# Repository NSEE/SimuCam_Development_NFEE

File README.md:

##SimuCam Development - N-FEE (LESIA/IAA)

# Repository Description - SimuCam/N-FEE
This repository manages the release of the software packages related with the SimuCam project, focusing on its N-FEE version, whose directly user  is the [LESIA (Laboratoire d’études spatiales et d’instrumentation en astrophysique)](https://lesia.obspm.fr/). This projet is a part of PLATO mission, and it is being developed by the NSEE (Núcleo de Sistemas Eletrônicos Embarcados) team, a laboratory that is part of [IMT (Instituto Mauá de Tecnologia)](https://maua.br/) at São Caetano do Sul, São Paulo, Brazil, in a partnership with [USP-IAG (Instituto de Astronomia, Geofísica e Ciências Atmosféricas)](https://www.iag.usp.br/) , funded by [FAPESP (Fundação de Amparo à Pesquisa do Estado de São Paulo )](https://fapesp.br/).

## Repository Contributors

- [Professor Vanderlei Cunha Parro - Laboratory and Project Coordinator](https://github.com/vparro) (2010-Today)
- [Professor Tiago Sanches da Silva - Software Architect, SW Team Leader and Developer](https://github.com/Tiagoeem) (2017-2020)
- [Engineer Rodrigo De Marca França - VHDL Architect and Developer](https://github.com/rodmarfran) (2017-Today)
- [Engineer Érico Lucas Marques - Project Manager and System Engineer](https://github.com/ericolucasm) (2018-Today)
- [Engineer Alexsander Deucher - SW Developer](https://github.com/adbtx) (2019-2020)
- [Engineer Ricardo Napoli - Test Engineer](https://github.com/rnapoli) (2019-2021)
- [Engineer Cassio Berni - SW Engineer](https://github.com/ccberni) (2019-2020)
- [Engineer Rafael Corsi Ferrão - Hardware Engineer](https://github.com/rafaelcorsi) (2011-2016) 
- [Engineer Thiago Pereira Ricciardi - SW Developer](https://github.com/thiagoricciardi) (2018-Today)

# SimuCam
The SimuCam is an electronic system with 8 independent SpaceWires links, emulating the behavior of PLATO’s cameras (N-FEE and F-FEE), and controlled by Ethernet.
SimuCam will be used by ﬁve diﬀerent teams in the PLATO consortium, each one in a diﬀerent situation, ranging from software development to system integration. 
From the user point of view, SimuCam is able to emulate 6 normal cameras and 4 fast cameras and a spacewire data generator.

SimuCam has 3 different versions, depending on its final use:

|#|Version ID|Final User Lab| Countries|
|:--:|:--:|--|--|
|1|SimuCam/N-FEE | [Lesia (Laboratoire d’études spatiales et d’instrumentation en astrophysique)](https://lesia.obspm.fr/), [IAA (Instituto Astrofísica Andalucía)](https://www.iaa.csic.es/en)| France, Spain
|2|SimuCam/F-FEE | [DLR (Deutsches Zentrum für Luft- und Raumfahrt)](https://www.dlr.de/DE/Home/home_node.html) | Germany
|3|SimuCam/Data Transmission | [IWF (Österreichische Akademie der Wissenschaften)(https://www.iwf.oeaw.ac.at/home/)], [INAF (Istituto Nazionale di Astrofisica)](http://www.inaf.it/it)|Austria, Italy

# PLATO (PLAnetary Transits and Oscillations of stars)
PLATO (PLAnetary Transits and Oscillations of stars) is the third medium-class mission in ESA's Cosmic Vision programme. Its objective is to find and study a large number of extrasolar planetary systems, with emphasis on the properties of terrestrial planets in the habitable zone around solar-like stars. PLATO has also been designed to investigate seismic activity in stars, enabling the precise characterisation of the planet host star, including its age.

More informmation about PLATO mission could be found in the Mission official [website](https://sci.esa.int/web/plato/).

# IMT (Instituto Mauá de Tecnologia)
IMT (Instituto Mauá de Tecnologia) is a private, non-proﬁt organization. Its main objective is to promote technical-scientiﬁc education, technological research and development aiming to provide highly qualiﬁed human resources to contribute to the socioeconomic development of Brazil. IMT was founded on December 11, 1961 its headquarters is located at Rua Pedro de Toledo, 1071 in São Paulo city. The institute maintains two units: the Centro Universitário and the Technical Services and Tests Center and two campi: one in São Paulo city and the other in São Caetano do Sul. The headquarter of the two units is located at IMT campus in São Caetano do Sul at Praça Maua, 1 with a constricted area of 130,000 m2, 12km from São Paulo city center. In this campus the Centro Universitário offers undergraduate courses in Engineering, Design, Administrations and Higher Education Certiﬁcate.

More informmation about IMT could be found in the Institute official [website](https://maua.br/).

# NSEE (Nucleo de Sistemas Eletrônicos Embarcados)
[NSEE (Nucleo de Sistemas Eletrônicos Embarcados)](https://maua.br/pesquisa/grupos-pesquisa/nucleo-sistemas-eletronicos-embarcados/), created on the initiative of the Mauá de Tecnologia Institute (IMT) based on participation in the initial version of INCT INEspaço, has developed research in the area of critical systems with direct application in the aerospace area. Its performance is related to the study of electronic systems that allow solving problems by meeting severe restrictions on communication speed, mass, consumption and real-time processing. Another area of expertise involves the development of multivariable control and signal processing systems, their algorithms and embedded implementations.

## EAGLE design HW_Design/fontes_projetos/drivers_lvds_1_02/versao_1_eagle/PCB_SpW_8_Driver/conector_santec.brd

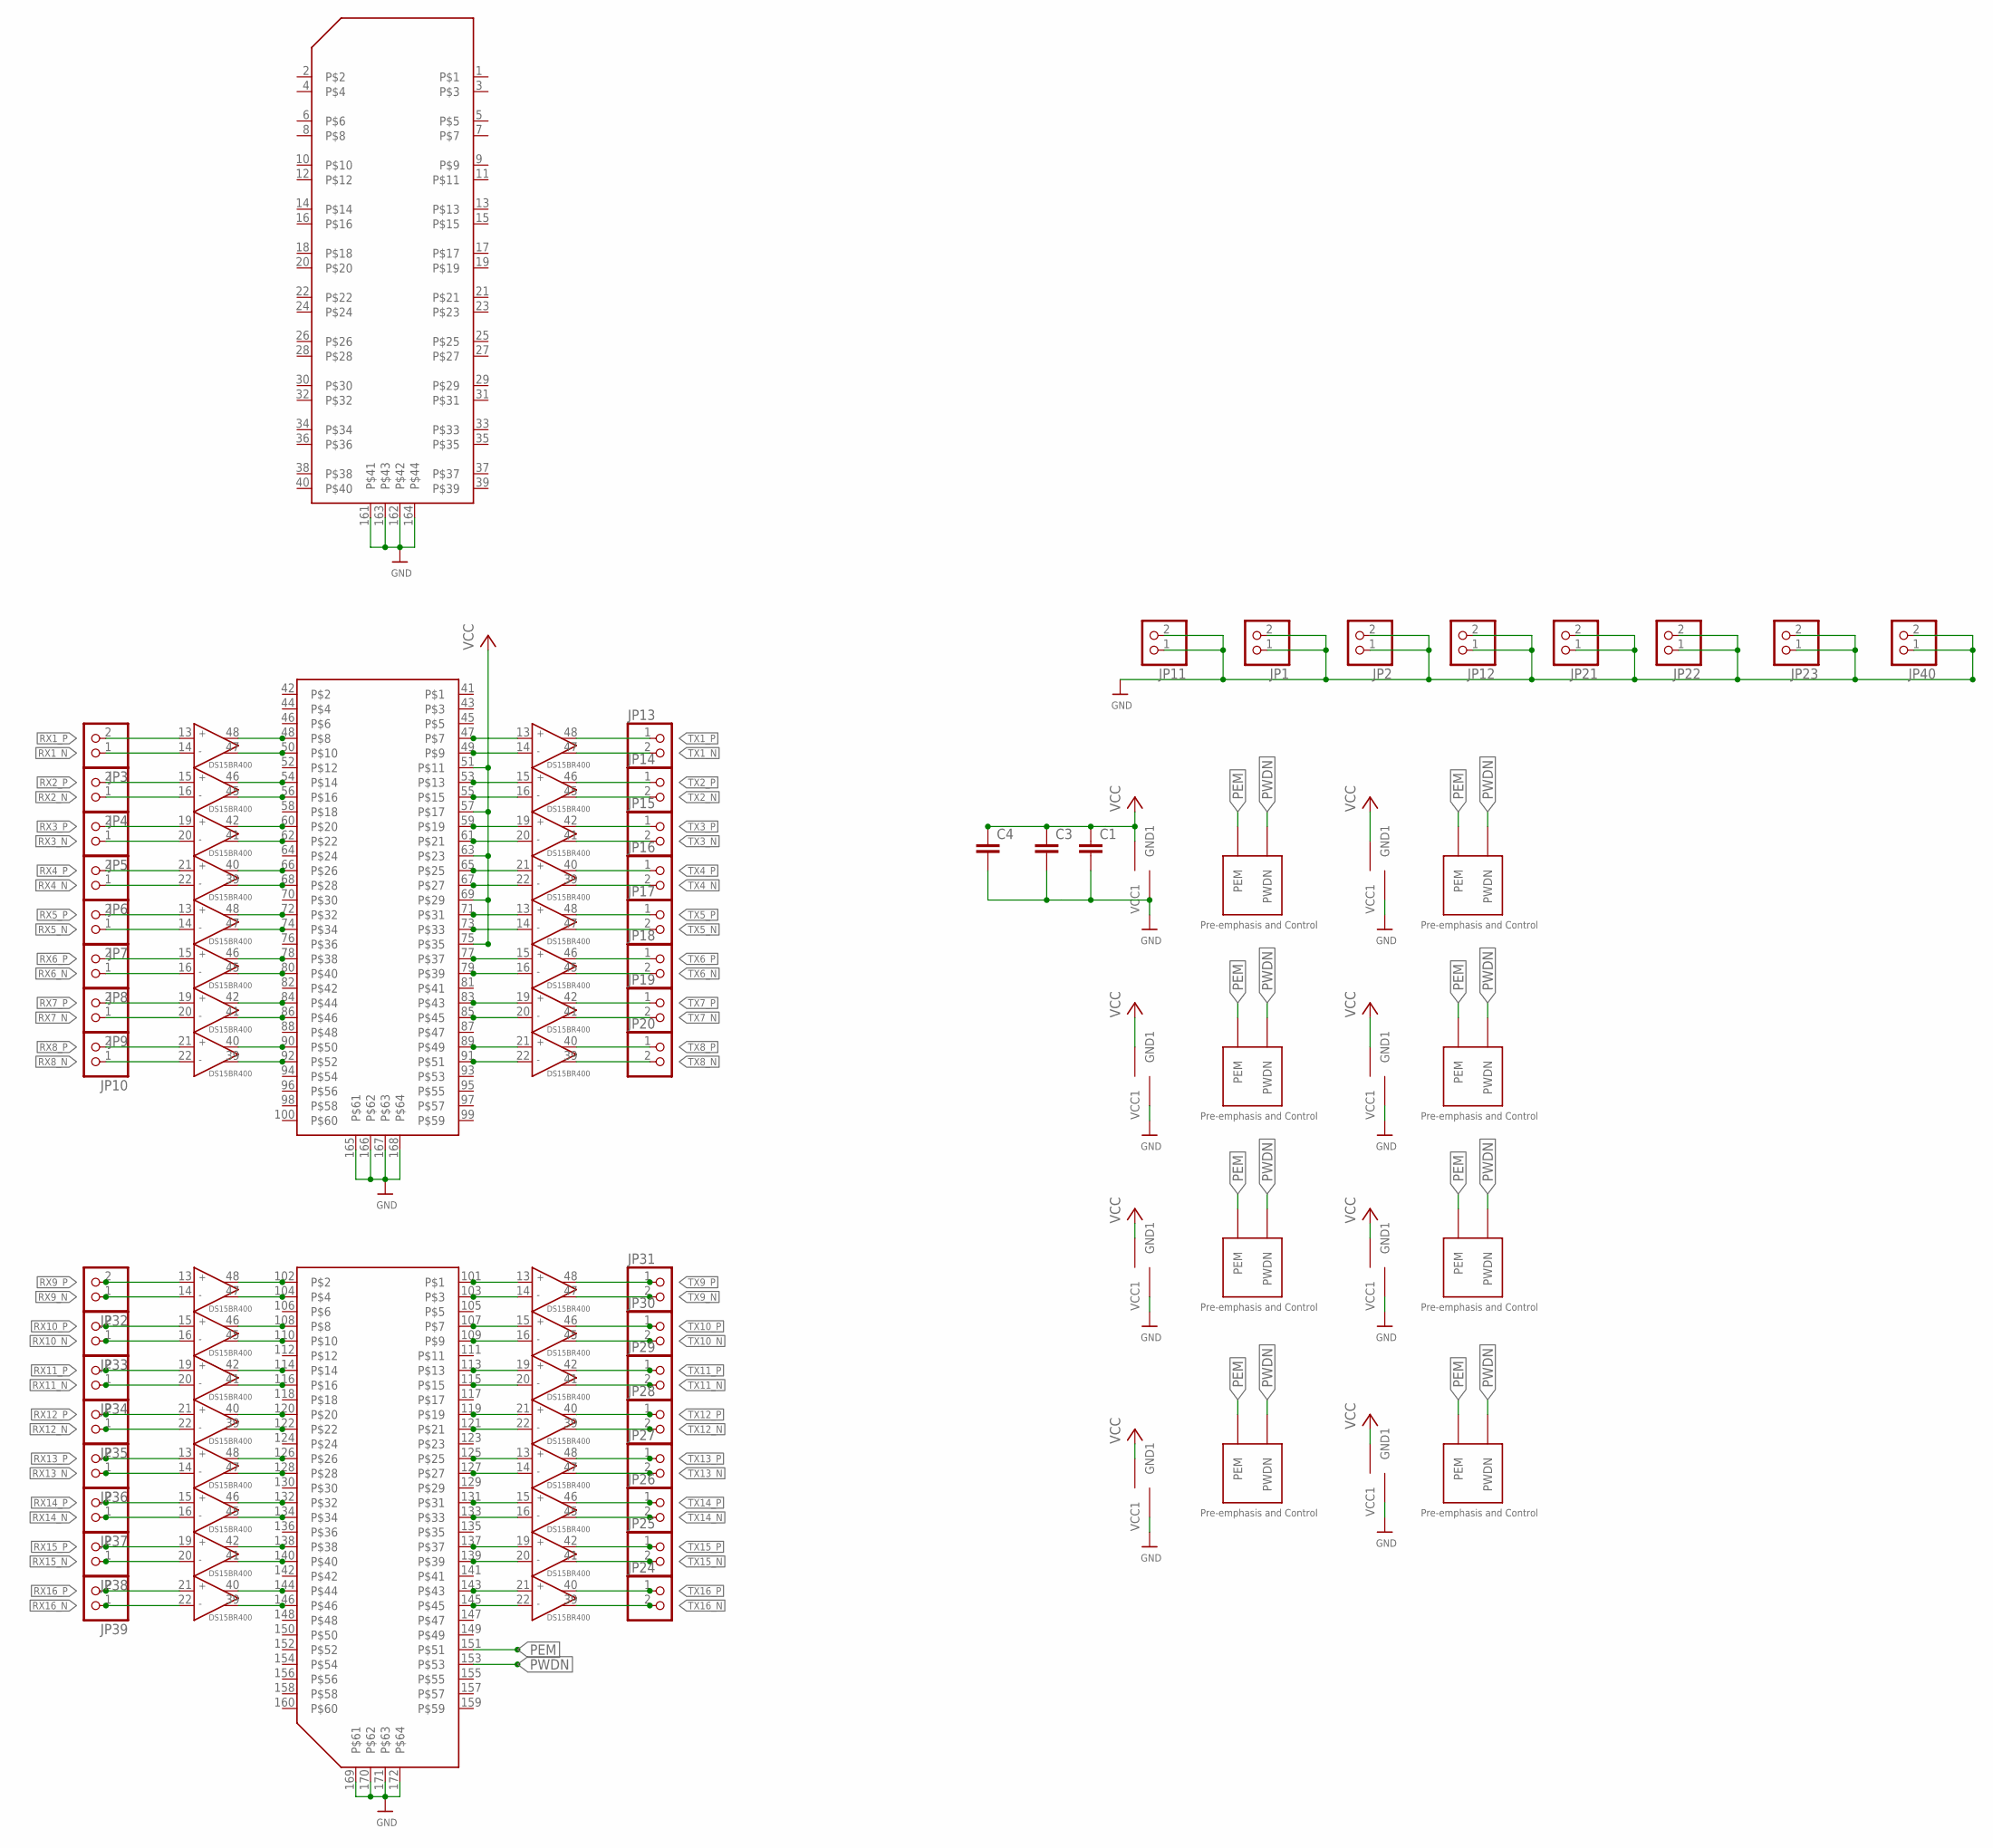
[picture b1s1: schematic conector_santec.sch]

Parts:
C1, C3, C4: C-EUC0603; C0603
JP1, JP2, JP3, JP4, JP5, JP6, JP7, JP8, JP9, JP10, JP11, JP12, JP13, JP14, JP15, JP16, JP17, JP18, JP19, JP20, JP21, JP22, JP23, JP24, JP25, JP26, JP27, JP28, JP29, JP30, JP31, JP32, JP33, JP34, JP35, JP36, JP37, JP38, JP39, JP40: HEADER-1X2ROUND; 1X02_ROUND
U$1: SAMTEC_ASP-122952-01; ASP-122952-01
U$4, U$6, U$7, U$8, U$15, U$16, U$17, U$18: DS15BR400; TQFP48

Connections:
GND: C1.2, C3.2, C4.2, JP1.1, JP1.2, JP2.1, JP2.2, JP11.1, JP11.2, JP12.1, JP12.2, JP21.1, JP21.2, JP22.1, JP22.2, JP23.1, JP23.2, JP40.1, JP40.2, U$1.161, U$1.162, U$1.163, U$1.164, U$1.165, U$1.166, U$1.167, U$1.168, U$1.169, U$1.170, U$1.171, U$1.172, U$4.8 (GND1), U$4.9 (GND1), U$4.17 (GND1), U$4.18 (GND1), U$4.23 (GND1), U$4.24 (GND1), U$4.37 (GND1), U$4.38 (GND1), U$4.43 (GND1), U$4.44 (GND1), U$6.8 (GND1), U$6.9 (GND1), U$6.17 (GND1), U$6.18 (GND1), U$6.23 (GND1), U$6.24 (GND1), U$6.37 (GND1), U$6.38 (GND1), U$6.43 (GND1), U$6.44 (GND1), U$7.8 (GND1), U$7.9 (GND1), U$7.17 (GND1), U$7.18 (GND1), U$7.23 (GND1), U$7.24 (GND1), U$7.37 (GND1), U$7.38 (GND1), U$7.43 (GND1), U$7.44 (GND1), U$8.8 (GND1), U$8.9 (GND1), U$8.17 (GND1), U$8.18 (GND1), U$8.23 (GND1), U$8.24 (GND1), U$8.37 (GND1), U$8.38 (GND1), U$8.43 (GND1), U$8.44 (GND1), U$15.8 (GND1), U$15.9 (GND1), U$15.17 (GND1), U$15.18 (GND1), U$15.23 (GND1), U$15.24 (GND1), U$15.37 (GND1), U$15.38 (GND1), U$15.43 (GND1), U$15.44 (GND1), U$16.8 (GND1), U$16.9 (GND1), U$16.17 (GND1), U$16.18 (GND1), U$16.23 (GND1), U$16.24 (GND1), U$16.37 (GND1), U$16.38 (GND1), U$16.43 (GND1), U$16.44 (GND1), U$17.8 (GND1), U$17.9 (GND1), U$17.17 (GND1), U$17.18 (GND1), U$17.23 (GND1), U$17.24 (GND1), U$17.37 (GND1), U$17.38 (GND1), U$17.43 (GND1), U$17.44 (GND1), U$18.8 (GND1), U$18.9 (GND1), U$18.17 (GND1), U$18.18 (GND1), U$18.23 (GND1), U$18.24 (GND1), U$18.37 (GND1), U$18.38 (GND1), U$18.43 (GND1), U$18.44 (GND1)
PEM: U$1.151, U$4.2 (PEM), U$6.2 (PEM), U$7.2 (PEM), U$8.2 (PEM), U$15.2 (PEM), U$16.2 (PEM), U$17.2 (PEM), U$18.2 (PEM)
PWDN: U$1.153, U$4.12 (PWDN), U$6.12 (PWDN), U$7.12 (PWDN), U$8.12 (PWDN), U$15.12 (PWDN), U$16.12 (PWDN), U$17.12 (PWDN), U$18.12 (PWDN)
RX1IN_N: U$1.50, U$7.47 (OUT-)
RX1IN_P: U$1.48, U$7.48 (OUT+)
RX1_N: JP3.1, U$7.14 (IN-)
RX1_P: JP3.2, U$7.13 (IN+)
RX2IN_N: U$1.56, U$7.45 (OUT-)
RX2IN_P: U$1.54, U$7.46 (OUT+)
RX2_N: JP4.1, U$7.16 (IN-)
RX2_P: JP4.2, U$7.15 (IN+)
RX3IN_N: U$1.62, U$7.41 (OUT-)
RX3IN_P: U$1.60, U$7.42 (OUT+)
RX3_N: JP5.1, U$7.20 (IN-)
RX3_P: JP5.2, U$7.19 (IN+)
RX4IN_N: U$1.68, U$7.39 (OUT-)
RX4IN_P: U$1.66, U$7.40 (OUT+)
RX4_N: JP6.1, U$7.22 (IN-)
RX4_P: JP6.2, U$7.21 (IN+)
RX5IN_N: U$1.74, U$8.47 (OUT-)
RX5IN_P: U$1.72, U$8.48 (OUT+)
RX5_N: JP7.1, U$8.14 (IN-)
RX5_P: JP7.2, U$8.13 (IN+)
RX6IN_N: U$1.80, U$8.45 (OUT-)
RX6IN_P: U$1.78, U$8.46 (OUT+)
RX6_N: JP8.1, U$8.16 (IN-)
RX6_P: JP8.2, U$8.15 (IN+)
RX7IN_N: U$1.86, U$8.41 (OUT-)
RX7IN_P: U$1.84, U$8.42 (OUT+)
RX7_N: JP9.1, U$8.20 (IN-)
RX7_P: JP9.2, U$8.19 (IN+)
RX8IN_N: U$1.92, U$8.39 (OUT-)
RX8IN_P: U$1.90, U$8.40 (OUT+)
RX8_N: JP10.1, U$8.22 (IN-)
RX8_P: JP10.2, U$8.21 (IN+)
RX9IN_N: U$1.104, U$17.47 (OUT-)
RX9IN_P: U$1.102, U$17.48 (OUT+)
RX9_N: JP32.1, U$17.14 (IN-)
RX9_P: JP32.2, U$17.13 (IN+)
RX10IN_N: U$1.110, U$17.45 (OUT-)
RX10IN_P: U$1.108, U$17.46 (OUT+)
RX10_N: JP33.1, U$17.16 (IN-)
RX10_P: JP33.2, U$17.15 (IN+)
RX11IN_N: U$1.116, U$17.41 (OUT-)
RX11IN_P: U$1.114, U$17.42 (OUT+)
RX11_N: JP34.1, U$17.20 (IN-)
RX11_P: JP34.2, U$17.19 (IN+)
RX12IN_N: U$1.122, U$17.39 (OUT-)
RX12IN_P: U$1.120, U$17.40 (OUT+)
RX12_N: JP35.1, U$17.22 (IN-)
RX12_P: JP35.2, U$17.21 (IN+)
RX13IN_N: U$1.128, U$18.47 (OUT-)
RX13IN_P: U$1.126, U$18.48 (OUT+)
RX13_N: JP36.1, U$18.14 (IN-)
RX13_P: JP36.2, U$18.13 (IN+)
RX14IN_N: U$1.134, U$18.45 (OUT-)
RX14IN_P: U$1.132, U$18.46 (OUT+)
RX14_N: JP37.1, U$18.16 (IN-)
RX14_P: JP37.2, U$18.15 (IN+)
RX15IN_N: U$1.140, U$18.41 (OUT-)
RX15IN_P: U$1.138, U$18.42 (OUT+)
RX15_N: JP38.1, U$18.20 (IN-)
RX15_P: JP38.2, U$18.19 (IN+)
RX16IN_N: U$1.146, U$18.39 (OUT-)
RX16IN_P: U$1.144, U$18.40 (OUT+)
RX16_N: JP39.1, U$18.22 (IN-)
RX16_P: JP39.2, U$18.21 (IN+)
TX1IN_N: U$1.49, U$4.14 (IN-)
TX1IN_P: U$1.47, U$4.13 (IN+)
TX1_N: JP13.2, U$4.47 (OUT-)
TX1_P: JP13.1, U$4.48 (OUT+)
TX2IN_N: U$1.55, U$4.16 (IN-)
TX2IN_P: U$1.53, U$4.15 (IN+)
TX2_N: JP14.2, U$4.45 (OUT-)
TX2_P: JP14.1, U$4.46 (OUT+)
TX3IN_N: U$1.61, U$4.20 (IN-)
TX3IN_P: U$1.59, U$4.19 (IN+)
TX3_N: JP15.2, U$4.41 (OUT-)
TX3_P: JP15.1, U$4.42 (OUT+)
TX4IN_N: U$1.67, U$4.22 (IN-)
TX4IN_P: U$1.65, U$4.21 (IN+)
TX4_N: JP16.2, U$4.39 (OUT-)
TX4_P: JP16.1, U$4.40 (OUT+)
TX5IN_N: U$1.73, U$6.14 (IN-)
TX5IN_P: U$1.71, U$6.13 (IN+)
TX5_N: JP17.2, U$6.47 (OUT-)
TX5_P: JP17.1, U$6.48 (OUT+)
TX6IN_N: U$1.79, U$6.16 (IN-)
TX6IN_P: U$1.77, U$6.15 (IN+)
TX6_N: JP18.2, U$6.45 (OUT-)
TX6_P: JP18.1, U$6.46 (OUT+)
TX7IN_N: U$1.85, U$6.20 (IN-)
TX7IN_P: U$1.83, U$6.19 (IN+)
TX7_N: JP19.2, U$6.41 (OUT-)
TX7_P: JP19.1, U$6.42 (OUT+)
TX8IN_N: U$1.91, U$6.22 (IN-)
TX8IN_P: U$1.89, U$6.21 (IN+)
TX8_N: JP20.2, U$6.39 (OUT-)
TX8_P: JP20.1, U$6.40 (OUT+)
TX9IN_N: U$1.103, U$15.14 (IN-)
TX9IN_P: U$1.101, U$15.13 (IN+)
TX9_N: JP31.2, U$15.47 (OUT-)
TX9_P: JP31.1, U$15.48 (OUT+)
TX10IN_N: U$1.109, U$15.16 (IN-)
TX10IN_P: U$1.107, U$15.15 (IN+)
TX10_N: JP30.2, U$15.45 (OUT-)
TX10_P: JP30.1, U$15.46 (OUT+)
TX11IN_N: U$1.115, U$15.20 (IN-)
TX11IN_P: U$1.113, U$15.19 (IN+)
TX11_N: JP29.2, U$15.41 (OUT-)
TX11_P: JP29.1, U$15.42 (OUT+)
TX12IN_N: U$1.121, U$15.22 (IN-)
TX12IN_P: U$1.119, U$15.21 (IN+)
TX12_N: JP28.2, U$15.39 (OUT-)
TX12_P: JP28.1, U$15.40 (OUT+)
TX13IN_N: U$1.127, U$16.14 (IN-)
TX13IN_P: U$1.125, U$16.13 (IN+)
TX13_N: JP27.2, U$16.47 (OUT-)
TX13_P: JP27.1, U$16.48 (OUT+)
TX14IN_N: U$1.133, U$16.16 (IN-)
TX14IN_P: U$1.131, U$16.15 (IN+)
TX14_N: JP26.2, U$16.45 (OUT-)
TX14_P: JP26.1, U$16.46 (OUT+)
TX15IN_N: U$1.139, U$16.20 (IN-)
TX15IN_P: U$1.137, U$16.19 (IN+)
TX15_N: JP25.2, U$16.41 (OUT-)
TX15_P: JP25.1, U$16.42 (OUT+)
TX16IN_N: U$1.145, U$16.22 (IN-)
TX16IN_P: U$1.143, U$16.21 (IN+)
TX16_N: JP24.2, U$16.39 (OUT-)
TX16_P: JP24.1, U$16.40 (OUT+)
VCC: C1.1, C3.1, C4.1, U$1.51, U$1.57, U$1.63, U$1.69, U$1.75, U$4.3 (VCC1), U$4.4 (VCC1), U$4.5 (VCC1), U$4.7 (VCC1), U$4.10 (VCC1), U$4.11 (VCC1), U$4.28 (VCC1), U$4.29 (VCC1), U$4.30 (VCC1), U$4.32 (VCC1), U$4.33 (VCC1), U$6.3 (VCC1), U$6.4 (VCC1), U$6.5 (VCC1), U$6.7 (VCC1), U$6.10 (VCC1), U$6.11 (VCC1), U$6.28 (VCC1), U$6.29 (VCC1), U$6.30 (VCC1), U$6.32 (VCC1), U$6.33 (VCC1), U$7.3 (VCC1), U$7.4 (VCC1), U$7.5 (VCC1), U$7.7 (VCC1), U$7.10 (VCC1), U$7.11 (VCC1), U$7.28 (VCC1), U$7.29 (VCC1), U$7.30 (VCC1), U$7.32 (VCC1), U$7.33 (VCC1), U$8.3 (VCC1), U$8.4 (VCC1), U$8.5 (VCC1), U$8.7 (VCC1), U$8.10 (VCC1), U$8.11 (VCC1), U$8.28 (VCC1), U$8.29 (VCC1), U$8.30 (VCC1), U$8.32 (VCC1), U$8.33 (VCC1), U$15.3 (VCC1), U$15.4 (VCC1), U$15.5 (VCC1), U$15.7 (VCC1), U$15.10 (VCC1), U$15.11 (VCC1), U$15.28 (VCC1), U$15.29 (VCC1), U$15.30 (VCC1), U$15.32 (VCC1), U$15.33 (VCC1), U$16.3 (VCC1), U$16.4 (VCC1), U$16.5 (VCC1), U$16.7 (VCC1), U$16.10 (VCC1), U$16.11 (VCC1), U$16.28 (VCC1), U$16.29 (VCC1), U$16.30 (VCC1), U$16.32 (VCC1), U$16.33 (VCC1), U$17.3 (VCC1), U$17.4 (VCC1), U$17.5 (VCC1), U$17.7 (VCC1), U$17.10 (VCC1), U$17.11 (VCC1), U$17.28 (VCC1), U$17.29 (VCC1), U$17.30 (VCC1), U$17.32 (VCC1), U$17.33 (VCC1), U$18.3 (VCC1), U$18.4 (VCC1), U$18.5 (VCC1), U$18.7 (VCC1), U$18.10 (VCC1), U$18.11 (VCC1), U$18.28 (VCC1), U$18.29 (VCC1), U$18.30 (VCC1), U$18.32 (VCC1), U$18.33 (VCC1)

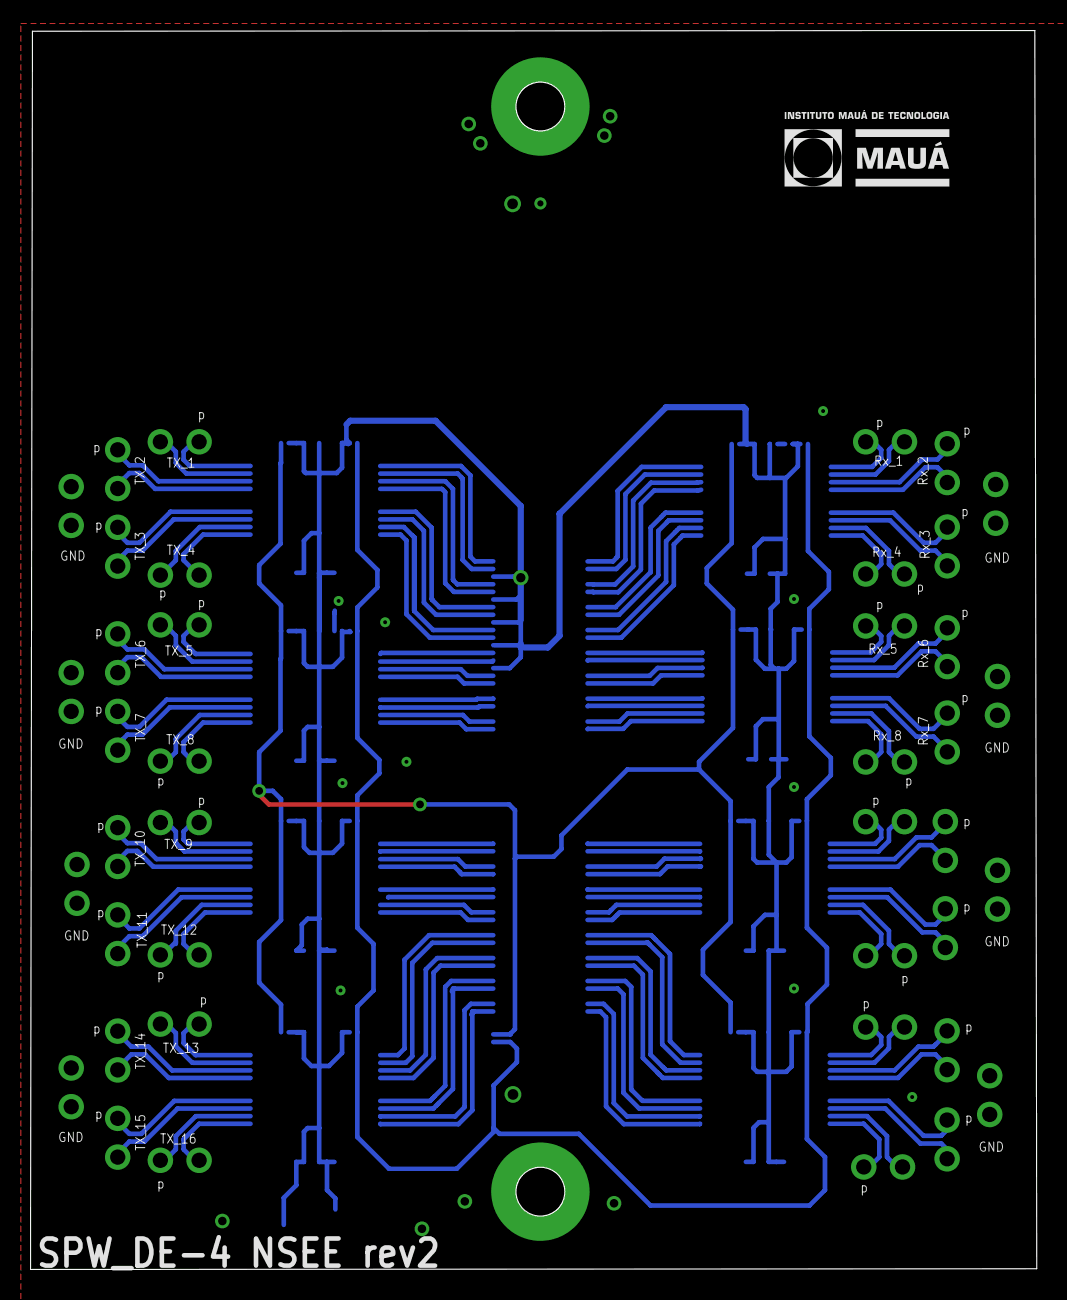
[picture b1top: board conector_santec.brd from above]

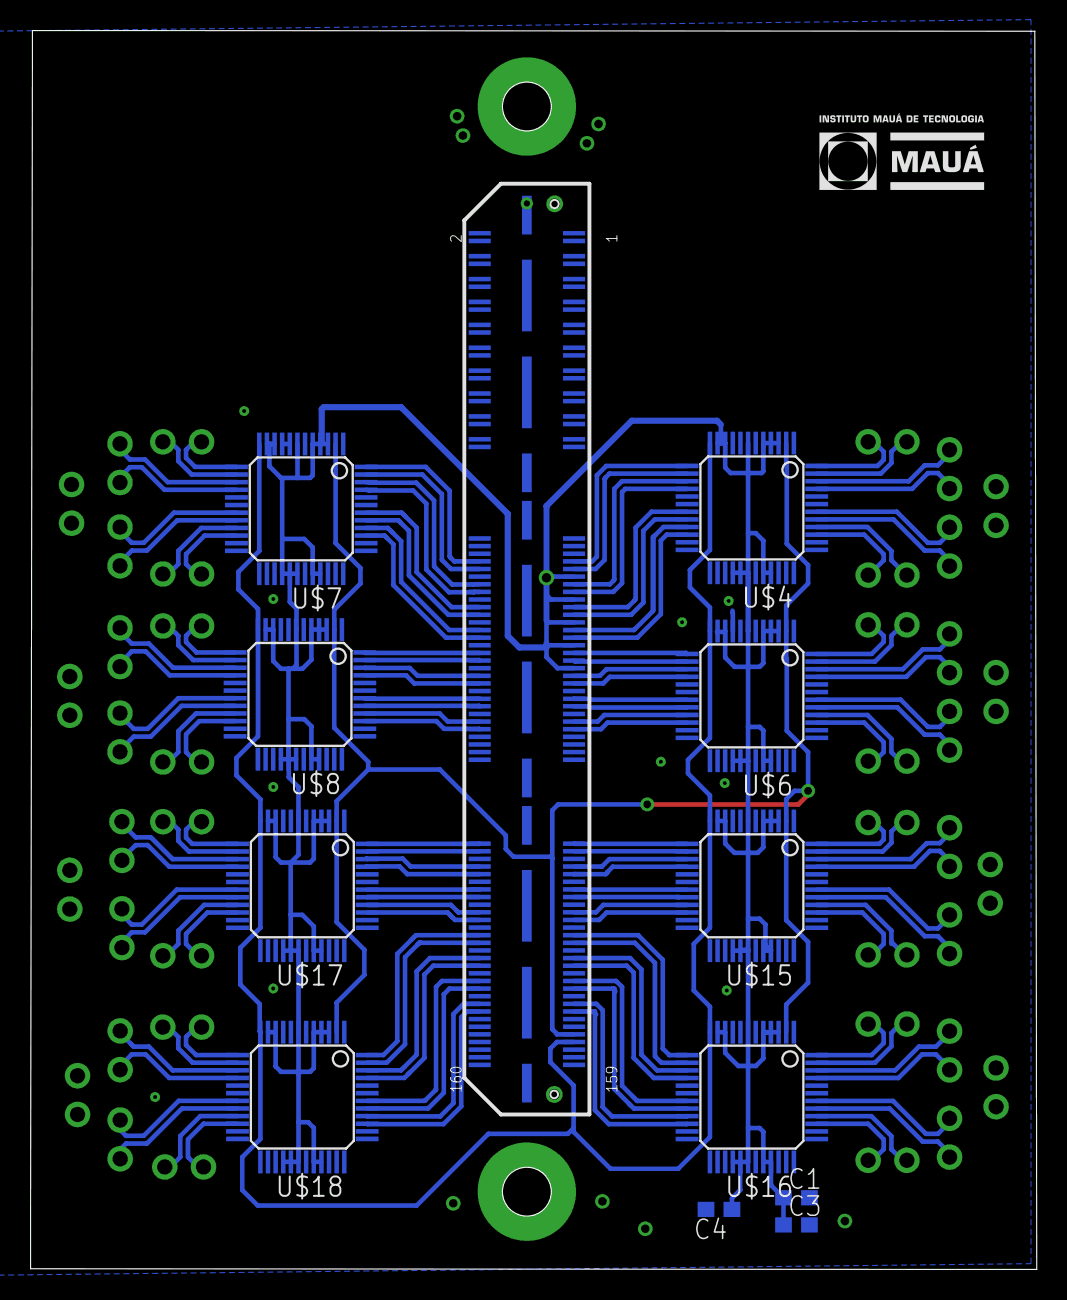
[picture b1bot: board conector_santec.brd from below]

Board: 2 copper layers, 65.9 x 81.2 mm, 54 parts (22 on the bottom side), 132 nets.

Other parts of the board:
U$2, U$3: LOGO_MAUA

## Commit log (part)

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2019-09-12 Tested and working
2019-09-12 Finished modifications in the API, to integration
2019-09-12 - HW and IRQ for DTC integration
2019-09-12 Add start - stop FTDI modeule
2019-09-13 Synthesized HW with correction in IRQ flag generation
2019-09-13 Build with HW merge, DTC not workin. HW issue.
2019-09-16 Modified Masking machine to support pattern generation
2019-09-16 DTC changes
2019-09-17 Proposed correction for usb3 tx, need to be tested
2019-09-18 Temporary commit, changing recovery action from FTDI error
2019-09-20 Sync Reset tested and ok
    Tested in SimuPus. Still needs state transition mechanism
2019-09-20 Fix in several HW libs, to remove Synthesis warnings
2019-09-20 Changed The NFEE Controller, and the message now goes from MEb directly to the FEEs
2019-09-21 Fixed Start of Payload [SIMULATED]
2019-09-23 Started developing the Timeout [IN DEVELOP]
2019-09-23 Error Flags correction
2019-09-24 Finished FTDI timeout and API modificiation
2019-09-24 Code ported from refactFee_updateHK
2019-09-24 Function working, preparing code cleaning
2019-09-24 New APIs tested, new HW crashed [CRASHED]
2019-09-24 Code migrated completely
2019-09-24 Improvement debug messages
2019-09-25 Corrected USB3 communication
2019-09-25 Synthetized HW with corrections in USB communications [SimuCam_R0_6ch_Ftdi_05] [SYNTHETIZED]
2019-09-26 Remove DMA Mutex, using only the queue to control the acess, and add B_Sync to the NFEE_CONTROLLER
2019-09-27 Updated COMM v1.8 to the last version
2019-09-28 Updated Rx Payload e Rx Header
2019-09-29 Partially Updated the Data Controller
2019-09-29 Partially Updated the Data Controller - Removed abort and timeout [SimuCam_6ch_salvation_v2_4]
2019-09-30 RMAP CONFIG UPDATE implemented
2019-10-01 Return of defective APIs
2019-10-01 check the sequence M_NFC_CONFIG_RESET
2019-10-02 Sync Reset solved
2019-10-03 Changed FTDI interrupt to 25 and modified the m1 clock bridge to 256b
2019-10-03 Synthesized HW with programable delay between qqwords in Ftdi Moduloe [SimuCam_6ch_Ftdi_6_delay]
2019-10-03 Compiled software for new HW [SimuCam_6ch_Ftdi_07_ComDTC_V0] [COMPILED]
2019-10-07 Synthetized HW with 16kiB for the FTDI buffer and timing correction for 5 channels [SimuCam_6ch_Ftdi_8] [SYNTHETIZED]
2019-10-07 Synthetized HW with 32kiB for the FTDI buffer and channel housekeeping correction [SimuCam_6ch_Ftdi_9] [SYNTHETIZED]
2019-10-14 Synthetized HW with corrections in Tiemcode and HK transmission [SimuCam_6ch_Ftdi_10] [SYNTHETIZED]
2019-10-21 Synthetized HW with more corrections and logic reduction [SimuCam_6ch_Ftdi_11] [SYNTHETIZED]
2019-10-21 Copied programming files to Program Flash
2019-10-28 Started New RST controller, working but need improvement
2019-10-30 First working proposal for RST. Need to be implemented in full project
2019-10-31 Modified Quartus Project to work with DE4-230 and DE4-530 boards
2019-11-14 Prepared files for error injection
2019-11-19 Finished developing the Error Injection APIs
2019-11-22 Finish integration of Reset Solution
2019-11-22 Started the API and Registers Table adaptation to RMAP NFEE MAP 1.0
2019-11-26 Finihsed modifications in the VBA Macros, need to adjust the map parameters
2019-11-26 Synthetized HW with NFEE RMAP map 1.0
2019-11-28 Synthetized first proposal of HW and FW for R1+ release [SYNTHETIZED] [R1+.0.0.0.0]
2019-12-07 Added API functions for Error Injection
2019-12-08 UPDATE EP using PUS command
2019-12-08 Add pre master sync signal in the Sync interrupt - Part 2
2019-12-08 New elf
2019-12-13 Sync source fix
2019-12-13 Fixing TIME_CONFIG
2019-12-16 Fix bug, ERROR_OFF, break before finish the case
2019-12-16 Fix rmap mod on
2020-01-30 New DMA architecture. FEEv3 and DTCv2 (Build OK)
2020-01-30 Corrected HW
2020-01-30 Synthetized R2b_0_0 hw from master
2020-01-30 R2_0_0_0_1_dmaOnly
2020-01-30 R2_0_0_0_1_dmaOnlyV4
2020-02-03 Add debug messages + change NFEE-COntrolerV3
2020-02-03 Transition and windowing finish logic
2020-02-03 Transition issue
2020-02-03 commit build affset
2020-02-04 Add error irq ftdi prints
2020-02-05 Finished Modifications in Sync Module, need to be synthetized and tested
2020-02-06 dma size change
2020-02-07 Put sync signal in debug pins
2020-02-07 Sinthetized L3.0.1 HW and generated L3.0.1.0.0 SW, with V-End modification
2020-02-13 Synthetized and generated correction in the v-end parameter
2020-02-14 Added memories fast test
2020-02-26 Synthetized hw with reset at each pre-sync
2020-02-27 Corrected version in SW
2020-02-27 Modified COMM to support isolated rmap memory (need testing)
2020-02-28 Finished isolation of NFEE RMAP. Need to be integrated in Qsys and tested
2020-03-06 Update sim_meb_task.c
    First commit, added echo mode subType and first configuration.
2020-03-06 Created Dummy Echoing Mode API (not working without HW)
2020-03-09 Synthetized HW with RMAP Echoing Registers
2020-03-09 Update names in ECHO MODE inside sim_meb_task
    Change the name "xEchoingModeConfig" to "xRmapEchoingModeConfig"
2020-03-10 Synthetized HW with isolated RMAP for tests
2020-03-11 Synthetized HW with modifications in packet count and overscan
2020-03-12 Synthetized new test HW
2020-03-12 Copied programming files
2020-03-13 Corrected pointer cast warning
2020-03-20 Modified behaviour to work with larger last_pkts
2020-03-27 Soved echoing issues, need to be integrated and tested
2020-03-27 RMAP Echoing working, need to be better integrated
2020-03-30 LuT Handler + Mutex DMA DTC
2020-04-04 Proposal for FTDI v2 done, need testing
2020-04-12 Finished RMAP mem area with direct memory access for the windowind area
2020-04-14 Update ECHOMODE
2020-04-14 HW stable for LUT transmission and finished API creation
2020-04-15 Finished integrating HW and SW
2020-04-17 Synthetized proposal for R2+ delivery HW
2020-04-17 Add SendPus with 512 chars size
2020-04-22 RMAP DUMP in MEB (Problem with TM SEND)
2020-04-23 Generated SW for Dynamic LUT Tests
2020-04-24 Cleaned VHDL code and remove COMMs 7 and 8 from the SW
2020-04-26 Added error flags mechanism in HW and SW
2020-04-28 Fix command Shutdown PUS 62->66
2020-04-28 Copied programming files to Program Flash DE4 folder
2020-04-29 Last Build Trap Pumping
2020-04-30 Finhished integration for R2+ release
2020-05-01 Parallel Trap 2 -> TRUE
2020-05-01 Finished solving conflicts
2020-05-15 SD Card DEBUG values overwriten with hard-coded values due to the SD Cards being not acessible for the time being
2020-05-19 Longer time to wait for mutex to transmit
2020-05-19 Add PUS command to change the data source
2020-05-22 RMAP NFEE Memory Area updated with latched spw errors flags and ccd_read_en control bit
2020-05-25 SSD and Pattern Mode finished
2020-05-28 Resintetized HW because of FTDI at 100 MHz
2020-05-29 Generated HW and SW with bugfix for JIRAs PLGSC-284 and PLGSC-285
2020-06-02 Serial Update
2020-06-04 STATUS REPORT New data format
2020-06-05 Corrected bug in the HW statistics
2020-06-05 RT change formula
2020-06-06 Modified Program Flash script, removed cable option to work with any cable number
2020-06-07 Added watchdog for memories initialization
2020-06-08 Created specific flash programmers for DE4 230, 530 and both
2020-06-08 Generated proposal for bugfix release L3.1.4.0.0 [SW]
2020-06-10 AVM Circular Buffer working in simulation. Need to be integrated in the COMM channel
2020-06-10 release L3.1.5.0.0 with correction in the last packet flag ready for functional tests
2020-06-11 Renamed programing files
2020-06-11 Initial impl Rmaps Master Sync Update
2020-06-12 RMAP master sync change - finished
2020-06-16 Generated SW and programming files
2020-06-22 Renamed old project files
2020-06-23 Updated Qsys with COMM v2
2020-06-27 FEE STATE SEND TO NUC
2020-06-28 Removed OCT from LVDS pins and setted pre-emphasys to maximum
2020-06-29 Finished proposal for Synchronization Provider Channel
2020-06-30 Finished proposition for SPWC 1.2
2020-07-01 Added timeout to the FTDI
2020-07-01 USB3 timeout working
2020-07-01 Corrected reset ans zero issues in FTDI
2020-07-07 Sintetized HW with new data transmitter and improved SpW Synchronizer
2020-07-22 Workaround issue solution for JIRA PLGS-309
2020-07-23 Added workaround for JIRA PLGSC-309 issue correction added
2020-07-24 Sinthetized HW with preliminary error injection features
2020-07-27 First integration with last SW/HW, need to be fixed
2020-07-28 Minor corrections on RMAP codec failure cases
2020-07-31 Synthetized HW with CBUF. Instable when more than one channel is used
2020-08-03 finished content and header error injection. Missing RMAP errors
2020-08-05 Added Error injection APIs
2020-08-12 ELF for DEBUG TRIG ERROR INJECTION
2020-08-24 Removed prints unnecessary
2020-09-05 Sinthetized HW with correction in content error injection and rmap error injection. Modified SW for content error injection and timecode error injection
2020-09-05 TimeCode Correction
2020-09-07 Last Issues Corretion Defaults
2020-09-11 Corrected issue 318
2020-09-18 PLGSC-320 Correction
2020-09-18 Prepared Release L5.0.2.0.0
2020-09-24 Resolutions of all issued ready, need to sinthetize HW
2020-09-26 Modified SW to use hardcoded defaults if the SD card is missing
2020-09-28 Modified Masking Machine to correct pixels overflow buffer behaviour
2020-09-29 Proposal for spw error injection integration done
2020-09-29 Proposal correction for JIRA PLGSC-337 done
2020-09-30 Proposal for TC_SCAM_WIN_ERR_ENABLE_WIN_PROG and TC_SCAM_WIN_ERR_DISABLE_WIN_PROG modifications
2020-10-01 Finished proposal for SpW error injection
2020-10-08 Correction for the Spw Error configurations
2020-10-16 Finished modifications in data transmitter
2020-10-17 Update ReadMe.txt
    Project info added.
2020-10-19 Update README.md
    Description updated.
2020-10-22 Sinthetized proposed HW for L5.0.5.0.0 with corrections in windowing and overscan features
2020-11-19 PLGSC-366 Remove Trigger
    TC_SCAMxx_RMAP_ERR_TRIG -> Removed TRIGGER from NIOS.
2020-11-27 Add new .elf
2021-01-29 Modications to Trap Pumping mode
2021-02-24 Increase robustness of error injection activation
2021-03-12 Added dynamic exposure number update
2021-03-15 Memory Filler component ready
2021-03-17 Added support to multiple cables to DE4 Program Flash Tool
2021-03-19 Update RMAP area to version V5 and solution for PLGSC-431 and Wrong CRC issues
2021-03-23 Added force payload length to the FTDI module to minimize problems involving diferent image sizes
2021-04-06 Corrections on SCOM and FTDI
2021-04-14 Separated RMAP Memory Area for SCOM
2021-04-14 Integration of modified HW done at Qsys level
2021-04-20 Synthetized HW for improved stability. HW failed to comply with desired stability
2021-04-23 Modified SW to support 3 retries at inicialization
2021-05-04 Modification on SpwError Generator to avoid latchs during sintetis
2021-05-05 New generation of HW to inprove stability
2021-05-11 Changed names for release
2021-05-27 Sinthetized new HW version wth content error injection correction
2021-06-03 Finished review and update of Defaults
2021-06-03 Corrected behaviour of TC_SCAM_SPW_RMAP_CONFIG_UPDATE
2021-06-03 Added aditional LUT transmission protection and review of error injection structures
2021-06-06 Added missing default for PUS and corrected the FEE_HK_UPDATE behaviour
2021-06-06 Corrected STATUS enums
2021-06-10 Corrected issue with reset command on CONFIG mode
2021-07-16 Update README.md
    General info update.
2021-10-29 Added option to clear the reset counter by software
2021-10-29 Added signal filter latch for the sync signal
2021-11-03 Correction with reset counter clear
2022-04-29 Deprecated RMAP_CONF_DUMP command and added DEFAULT_DUMP and CONF_DUMP commands
2023-02-19 Modifications in the HW masking machine to improve overscan transmission
2023-07-17 Modifications to imporove system overall stability
